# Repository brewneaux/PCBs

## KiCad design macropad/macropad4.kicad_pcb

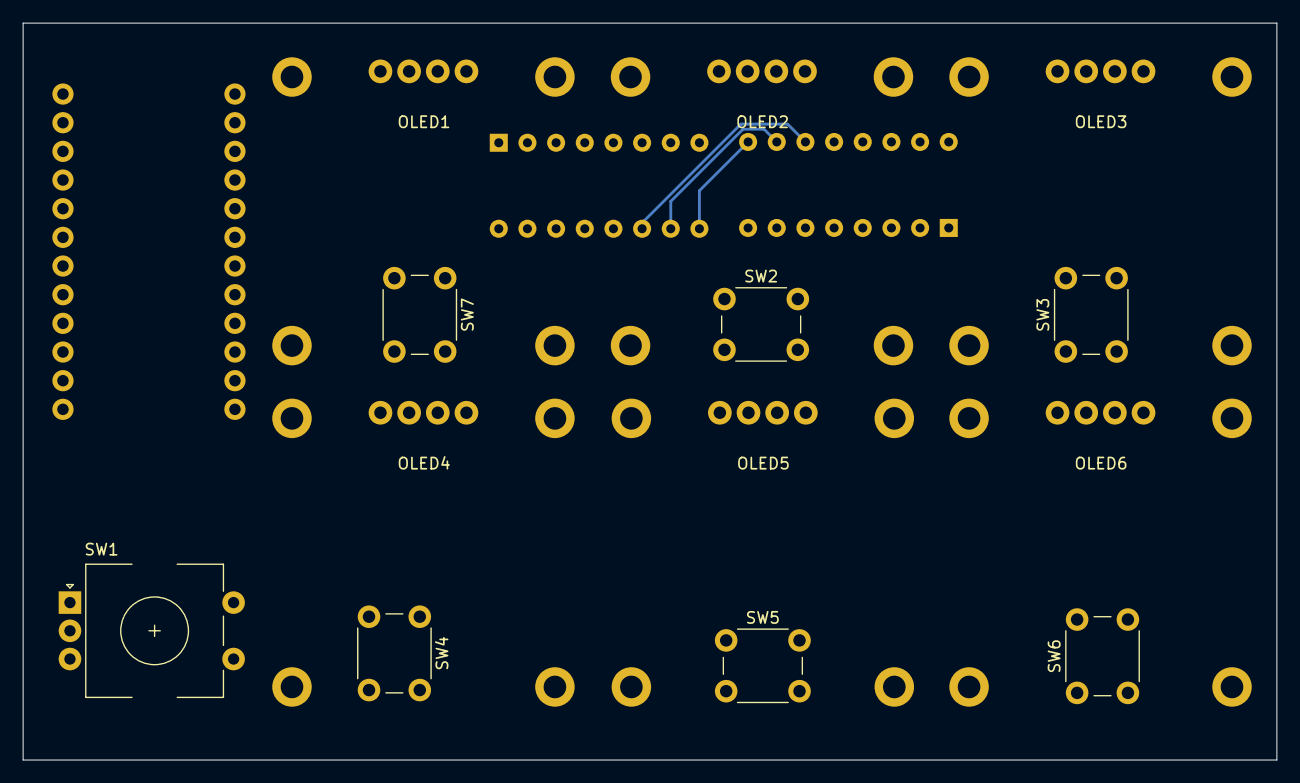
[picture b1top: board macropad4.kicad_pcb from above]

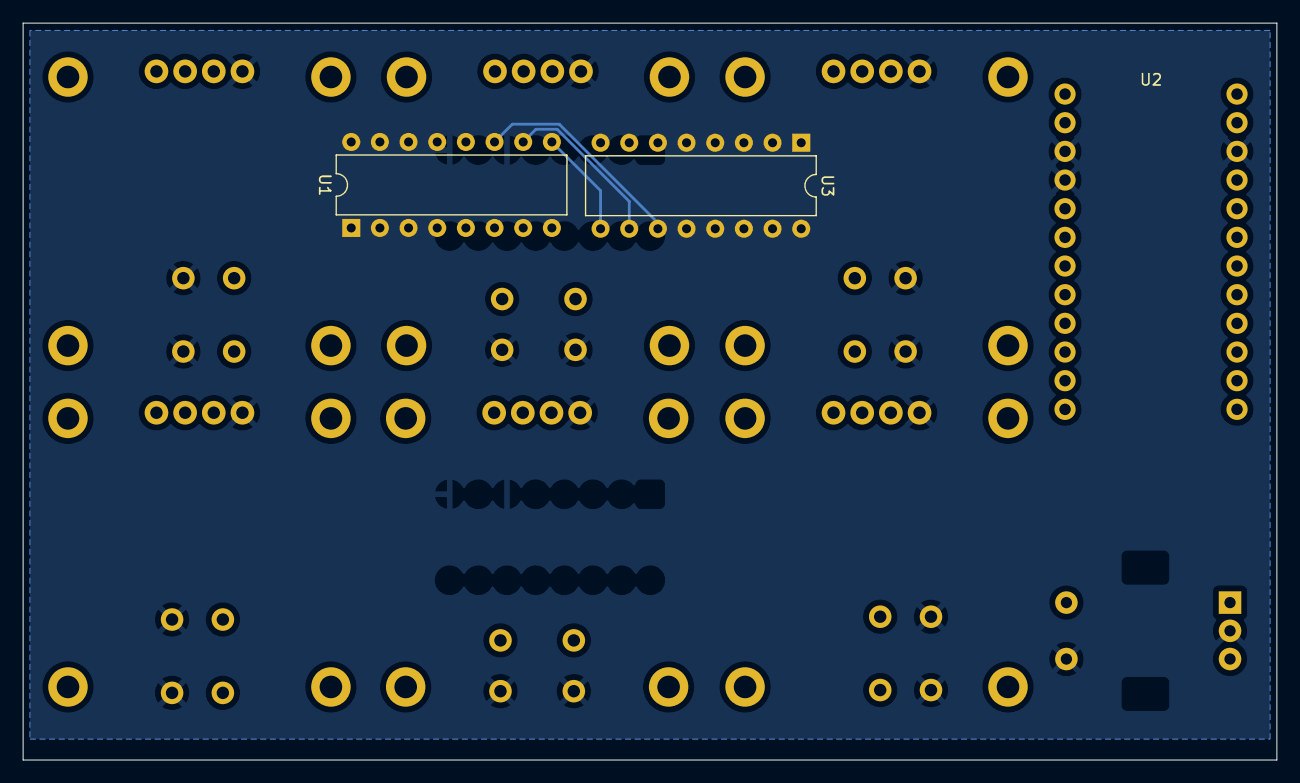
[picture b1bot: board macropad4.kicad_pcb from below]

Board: 2 copper layers, 111.1 x 65.3 mm, 16 parts (3 on the bottom side), 23 nets.

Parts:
OLED1, OLED2, OLED3, OLED4, OLED5, OLED6: ssd1306_0.96in; SSD1306_0.96in
SW1: RotaryEncoder_Switch; RotaryEncoder_Alps_EC11E-Switch_Vertical_H20mm
SW2, SW3, SW4, SW5, SW6, SW7: SW_SPST; SW_PUSH_6mm_H4.3mm
U1, U3: 74HC4051; DIP-16_W7.62mm
U2: SparkFun_Pro_Micro_-_RP2040; Sparkfun Pro Micro - RP2040

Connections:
3v3: OLED1.2 (VCC), OLED2.2 (VCC), OLED3.2 (VCC), OLED4.2 (VCC), OLED5.2 (VCC), OLED6.2 (VCC), U1.16 (VCC), U2.21 (VCC), U3.16 (VCC)
ADDR0: U1.11 (S0), U2.12 (GPIO9), U3.11 (S0)
ADDR1: U1.10 (S1), U2.11 (GPIO8), U3.10 (S1)
ADDR2: U1.9 (S2), U2.10 (GPIO7), U3.9 (S2)
GND: OLED1.1 (GND), OLED2.1 (GND), OLED3.1 (GND), OLED4.1 (GND), OLED5.1 (GND), OLED6.1 (GND), SW1.C, SW1.S1, SW2.2 (B), SW3.2 (B), SW4.2 (B), SW5.2 (B), SW6.2 (B), SW7.2 (B), U1.6 (~E), U1.8 (GND), U2.3 (GND), U2.4 (GND), U2.22 (GND), U3.6 (~E), U3.8 (GND)
OLED_SDA: U1.3 (A), U2.15 (GPIO20)
OLED_SDA_1: OLED1.4 (SDA), U1.1 (A4)
OLED_SDA_2: OLED3.4 (SDA), U1.5 (A5)
OLED_SDA_3: OLED5.4 (SDA), U1.13 (A0)
OLED_SDA_4: OLED2.4 (SDA), U1.14 (A1)
OLED_SDA_5: OLED4.4 (SDA), U1.15 (A2)
OLED_SDA_6: OLED6.4 (SDA), U1.12 (A3)
ROTARY_A: SW1.A, U2.7 (GPIO4)
ROTARY_B: SW1.B, U2.8 (GPIO5)
ROTARY_SW: SW1.S2, U2.6 (GPIO3)
SCL: OLED1.3 (SCL), OLED2.3 (SCL), OLED3.3 (SCL), OLED4.3 (SCL), OLED5.3 (SCL), OLED6.3 (SCL), U2.13 (GPIO21)
SWITCH_SIG: U2.9 (GPIO6), U3.3 (A)
SW_1: SW7.1 (A), U3.1 (A4)
SW_2: SW5.1 (A), U3.5 (A5)
SW_3: SW3.1 (A), U3.12 (A3)
SW_4: SW6.1 (A), U3.14 (A1)
SW_5: SW4.1 (A), U3.15 (A2)
SW_6: SW2.1 (A), U3.13 (A0)

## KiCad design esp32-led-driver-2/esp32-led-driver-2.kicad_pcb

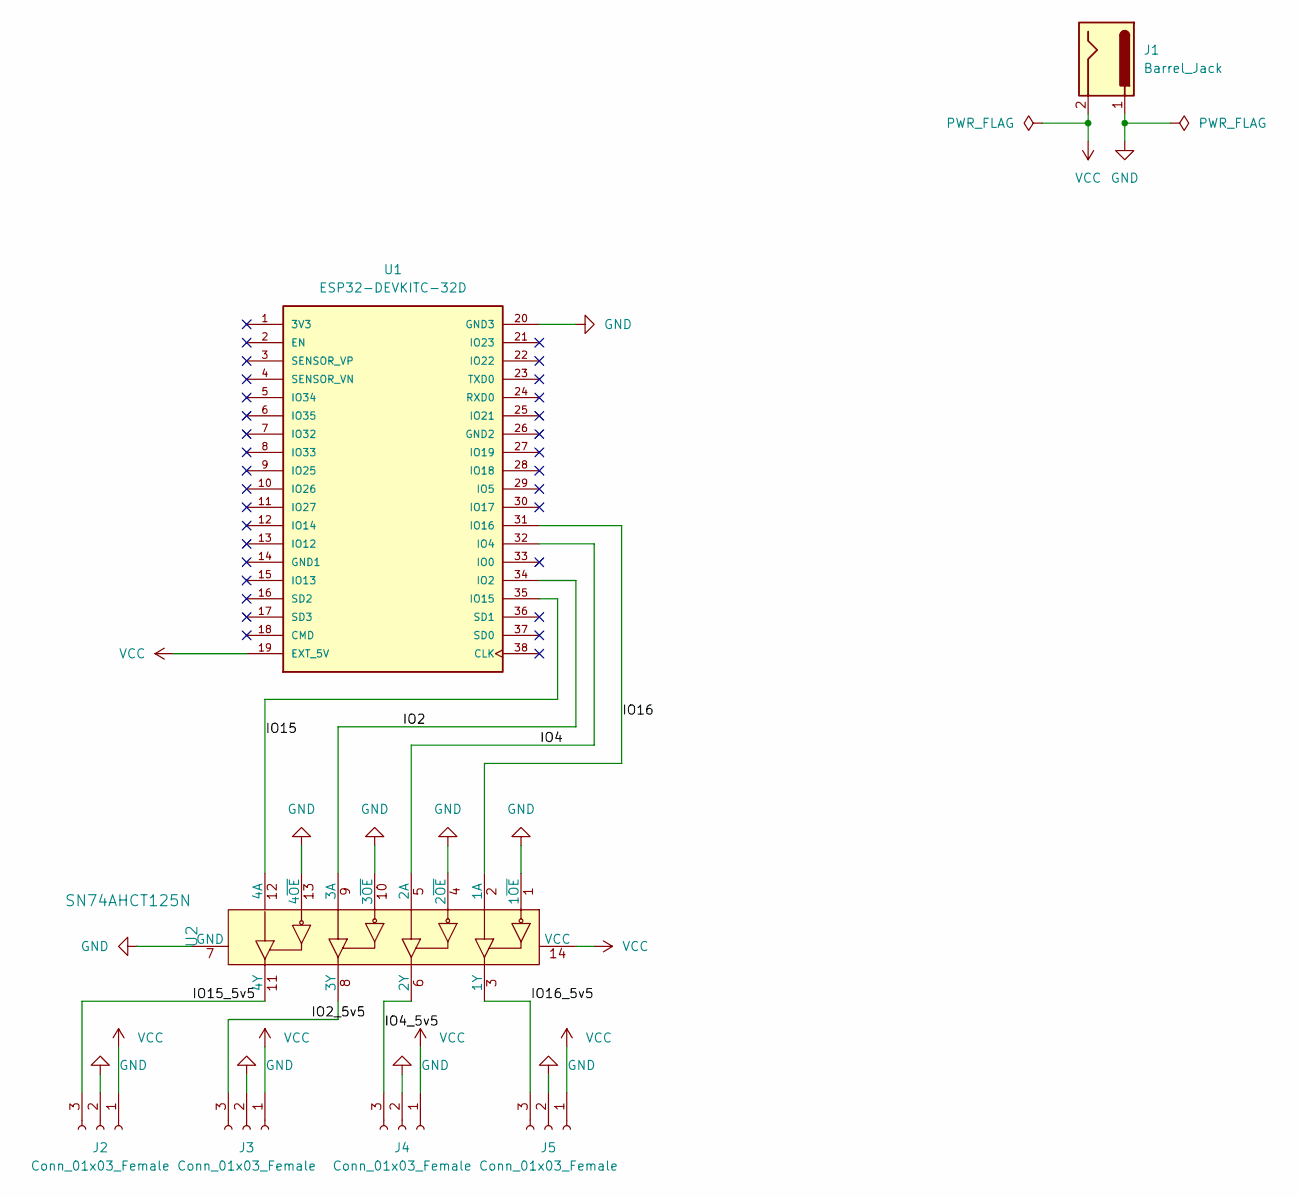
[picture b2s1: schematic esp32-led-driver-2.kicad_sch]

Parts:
J1: Barrel_Jack; SolderPad_2_2.0_2.0mm
J2, J3, J4, J5: Conn_01x03_Female; SolderPad_3_2.0_2.0mm
U1: ESP32-DEVKITC-32D; MODULE_ESP32-DEVKITC-32D; PARTREV 4
U2: SN74AHCT125N; DIP-14_W3mm; MPN SN74AHCT125N; Digi-Key_PN 296-4655-5-ND

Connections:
/IO2: U1.34 (IO2), U2.9 (3A)
/IO2_5v5: J3.3, U2.8 (3Y)
/IO4: U1.32 (IO4), U2.5 (2A)
/IO4_5v5: J4.3, U2.6 (2Y)
/IO15: U1.35 (IO15), U2.12 (4A)
/IO15_5v5: J2.3, U2.11 (4Y)
/IO16: U1.31 (IO16), U2.2 (1A)
/IO16_5v5: J5.3, U2.3 (1Y)
GND: J1.1, J2.2, J3.2, J4.2, J5.2, U1.20 (GND3), U2.1 (1~OE), U2.4 (2~OE), U2.7 (GND), U2.10 (3~OE), U2.13 (4~OE)
VCC: J1.2, J2.1, J3.1, J4.1, J5.1, U1.19 (EXT_5V), U2.14 (VCC)

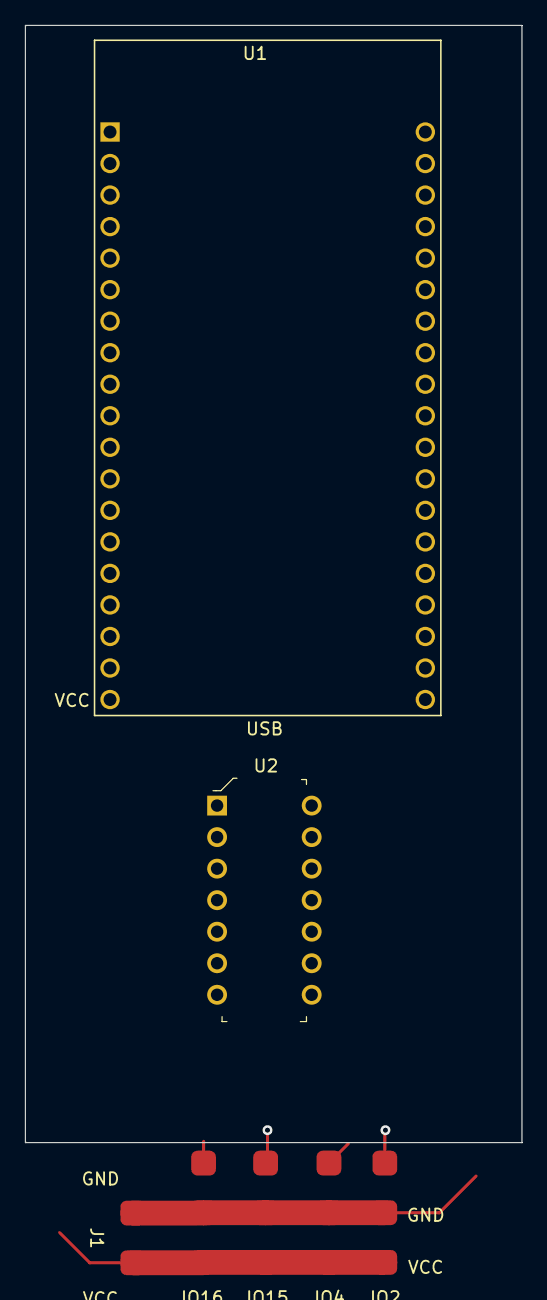
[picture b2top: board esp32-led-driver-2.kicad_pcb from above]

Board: 2 copper layers, 7 parts (0 on the bottom side), 10 nets.

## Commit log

2022-12-15 Initial
2022-12-28 Added macropad
